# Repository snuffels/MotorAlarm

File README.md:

# MotorAlarm
The MotorAlarm is an temprature alarm for combustion engines. I made it for the diesel
engine of my boat. The temprature sensor DS18B20 has a metal shell and can be put in 
the cooling water outlet of the engine.
The project is based on an Arduino pro mini (a future version may be based on an
atmel 328 chip). There is a schematic and board in eagle. There is also a openScad
file so you can print the case.
The display is a sainsmart 1.8" tft.
When the engine is not running the display displays the wind in knots and Beaufort
and also draws a graph of the wind trend.
The engine running or not is detected by a 12V (12V=engine running) input to an 
optocoupler to protect the arduino.
The wind data is received from a NASA NMEA 0183 wind head.
The alarm output is with an open collector pnp transistor. So you can add a 12V 
buzzer.
There is no voltage regulator in the board, I have a seperate 5V net onboard for
the arduino gatgets.

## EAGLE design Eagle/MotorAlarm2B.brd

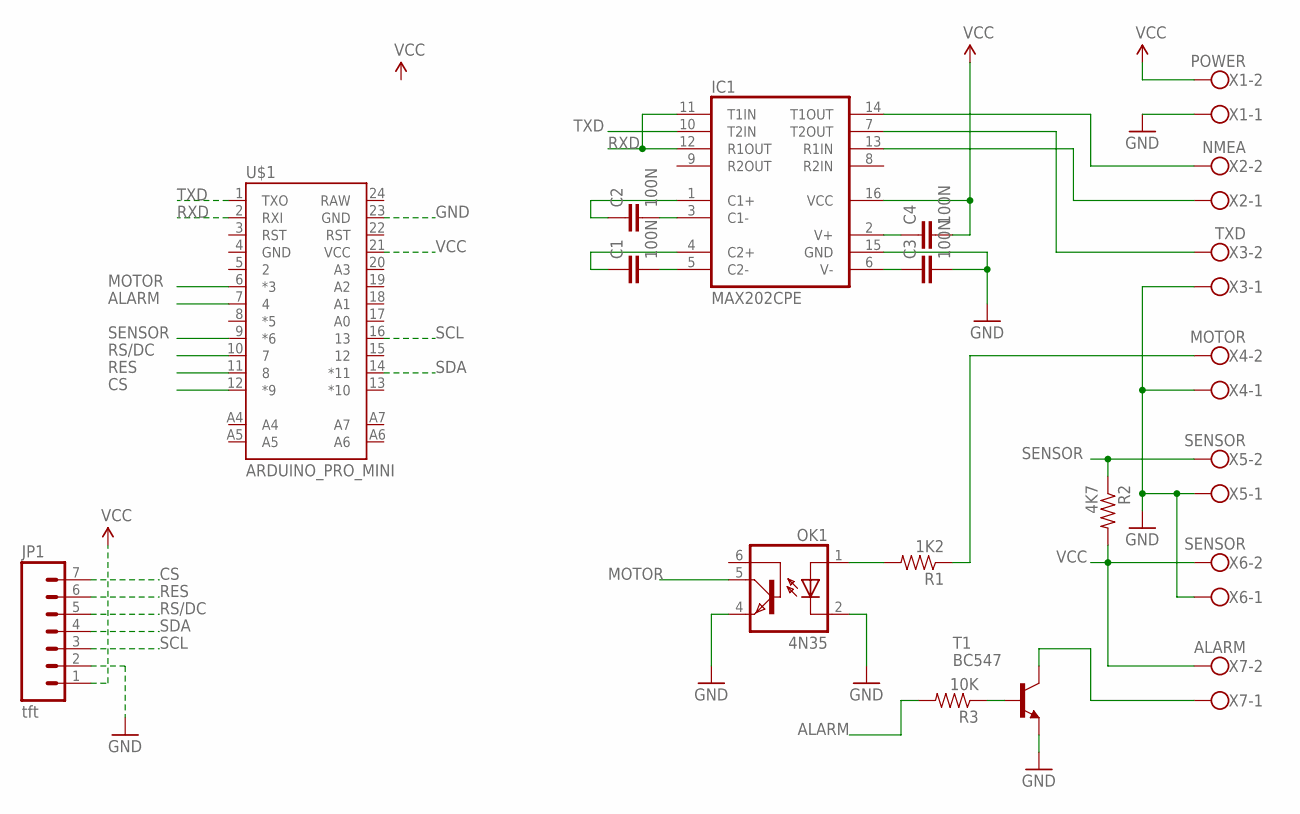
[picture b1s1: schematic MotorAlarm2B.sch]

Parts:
C1, C2, C3, C4: 100N; CAP-PTH-SMALL
IC1: MAX202CPE; DIL16
JP1: tft; 1X07
OK1: 4N35; DIL06
R1: 1K2; AXIAL-0.4
R2: 4K7; AXIAL-0.4
R3: 10K; AXIAL-0.4
T1: BC547; TO92
U$1: ARDUINO_PRO_MINI
X1: POWER; W237-102
X2: NMEA; W237-102
X3: TXD; W237-102
X4: MOTOR; W237-102
X5, X6: SENSOR; W237-102
X7: ALARM; W237-102

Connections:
ALARM: R3.P$2 (2), U$1.7 (4)
CS: JP1.7, U$1.12 (*9)
GND: C3.2, IC1.15 (GND), JP1.2, OK1.2 (C), OK1.4 (EMI), T1.1 (E), U$1.23 (GND), X1.1, X3.1, X4.1, X5.1, X6.1
MOTOR: OK1.5 (COL), U$1.6 (*3)
unnamed: C1.2, IC1.5 (C2-)
unnamed: C1.1, IC1.4 (C2+)
unnamed: C2.2, IC1.3 (C1-)
unnamed: C2.1, IC1.1 (C1+)
unnamed: OK1.1 (A), R1.P$2 (2)
unnamed: IC1.14 (T1OUT), X2.2
unnamed: IC1.13 (R1IN), X2.1
unnamed: IC1.7 (T2OUT), X3.2
unnamed: R1.P$1 (1), X4.2
unnamed: T1.3 (C), X7.1
unnamed: R3.P$1 (1), T1.2 (B)
RES: JP1.6, U$1.11 (8)
RS/DC: JP1.5, U$1.10 (7)
RXD: IC1.11 (T1IN), IC1.12 (R1OUT), U$1.2 (RXI)
SCL: JP1.3, U$1.16 (13)
SDA: JP1.4, U$1.14 (*11)
SENSOR: R2.P$1 (1), U$1.9 (*6), X5.2
TXD: IC1.10 (T2IN), U$1.1 (TXO)
V+: C4.1, IC1.2 (V+)
V-: C3.1, IC1.6 (V-)
VCC: C4.2, IC1.16 (VCC), JP1.1, R2.P$2 (2), U$1.21 (VCC), X1.2, X6.2, X7.2

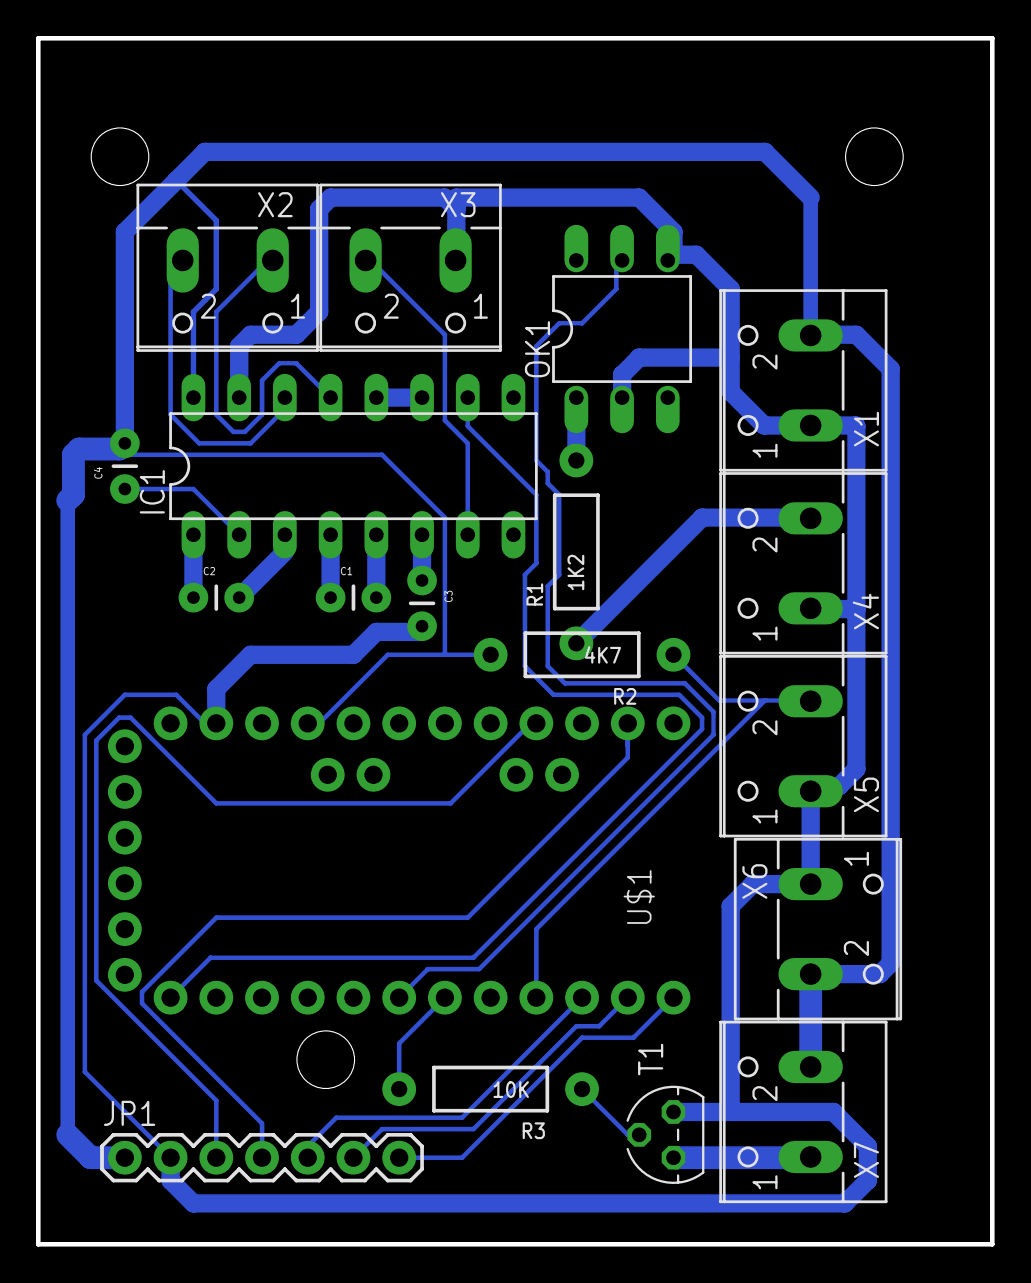
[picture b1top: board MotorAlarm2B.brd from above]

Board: 2 copper layers, 53.0 x 67.0 mm, 19 parts (0 on the bottom side), 25 nets.

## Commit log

2015-06-20 Create LICENSE
2015-06-20 Added description to README.md

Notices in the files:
parts and their libraries:
SparkFun-Boards: Licensing: Creative Commons ShareAlike 4.0 International - https://creativecommons.org/licenses/by-sa/4.0
